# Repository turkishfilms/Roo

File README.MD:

# Roo

The Roo is a 28-key wireless split ergonomic keyboard running zmk.

This keyboard was generated using ergogen (link to ergogen)

The Original Ergogen output as well as the routed pcb files are available to tweak
as you'd like.

The default Keymap right now is an incomplete colemak dh.

## Coming Soon:
- Roo Bill Of Materials (BOM)
- QWERTY default keymap
- My full keymap 
- Hands_Down Neu
- 3d printable body files
- 3d printable case files

## Future Plans
- Hopefully a Random Number Key (ZMK devleopment incoming)
- Possibly a password enabled password manager built into the keyboard
- Parametric case and body files
- Wireless Charging
- Wireless Charging Case

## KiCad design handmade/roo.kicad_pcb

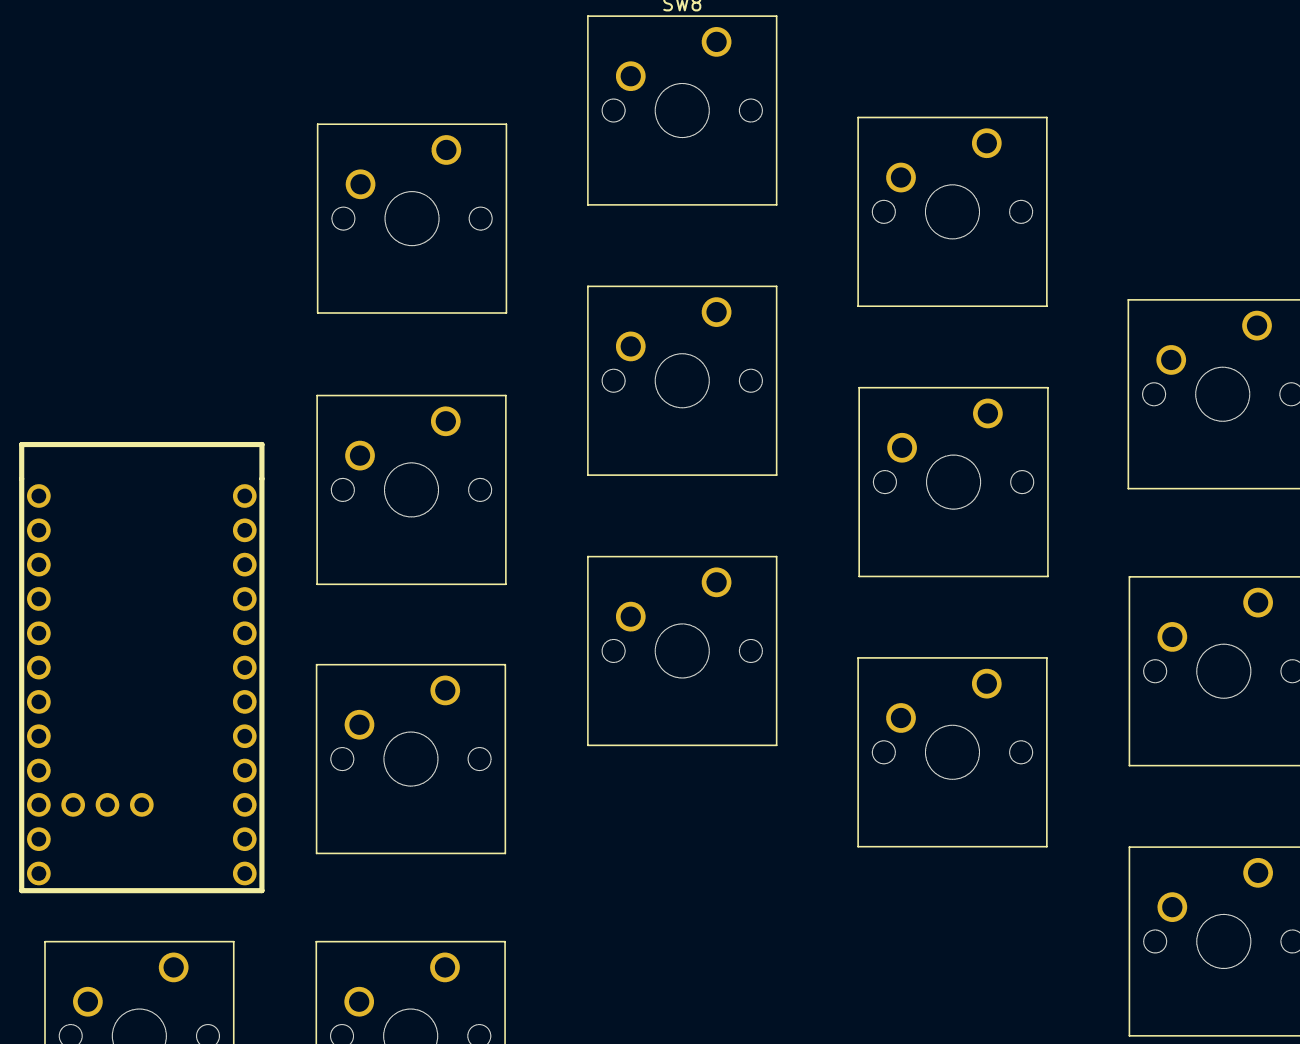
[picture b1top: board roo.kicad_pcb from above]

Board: 2 copper layers, 15 parts (0 on the bottom side), 15 nets, no tracks yet.

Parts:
SW1, SW2, SW3, SW4, SW5, SW6, SW7, SW8, SW9, SW10, SW11, SW12, SW13, SW14: SW_SPST; SW_Cherry_MX_1.00u_PCB
U1: nice_nano

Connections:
/K1: SW1.1 (A), U1.7 (P0.22)
/K2: SW2.1 (A), U1.8 (P0.24)
/K3: SW3.1 (A), U1.9 (P1.00)
/K4: SW4.1 (A), U1.10 (P0.11)
/K5: SW5.1 (A), U1.11 (P1.04)
/K6: SW6.1 (A), U1.12 (P1.06)
/K7: SW7.1 (A), U1.20 (AIN7/P0.31)
/K8: SW8.1 (A), U1.19 (AIN5/P0.29)
/K9: SW9.1 (A), U1.18 (AIN0/P0.02)
/K10: SW10.1 (A), U1.17 (P1.15)
/K11: SW11.1 (A), U1.16 (P1.13)
/K12: SW12.1 (A), U1.15 (P1.11)
/K13: SW13.1 (A), U1.14 (NFC2/P0.10)
/K14: SW14.1 (A), U1.13 (NFC1/P0.09)
GND: SW1.2 (B), SW2.2 (B), SW3.2 (B), SW4.2 (B), SW5.2 (B), SW6.2 (B), SW7.2 (B), SW8.2 (B), SW9.2 (B), SW10.2 (B), SW11.2 (B), SW12.2 (B), SW13.2 (B), SW14.2 (B)

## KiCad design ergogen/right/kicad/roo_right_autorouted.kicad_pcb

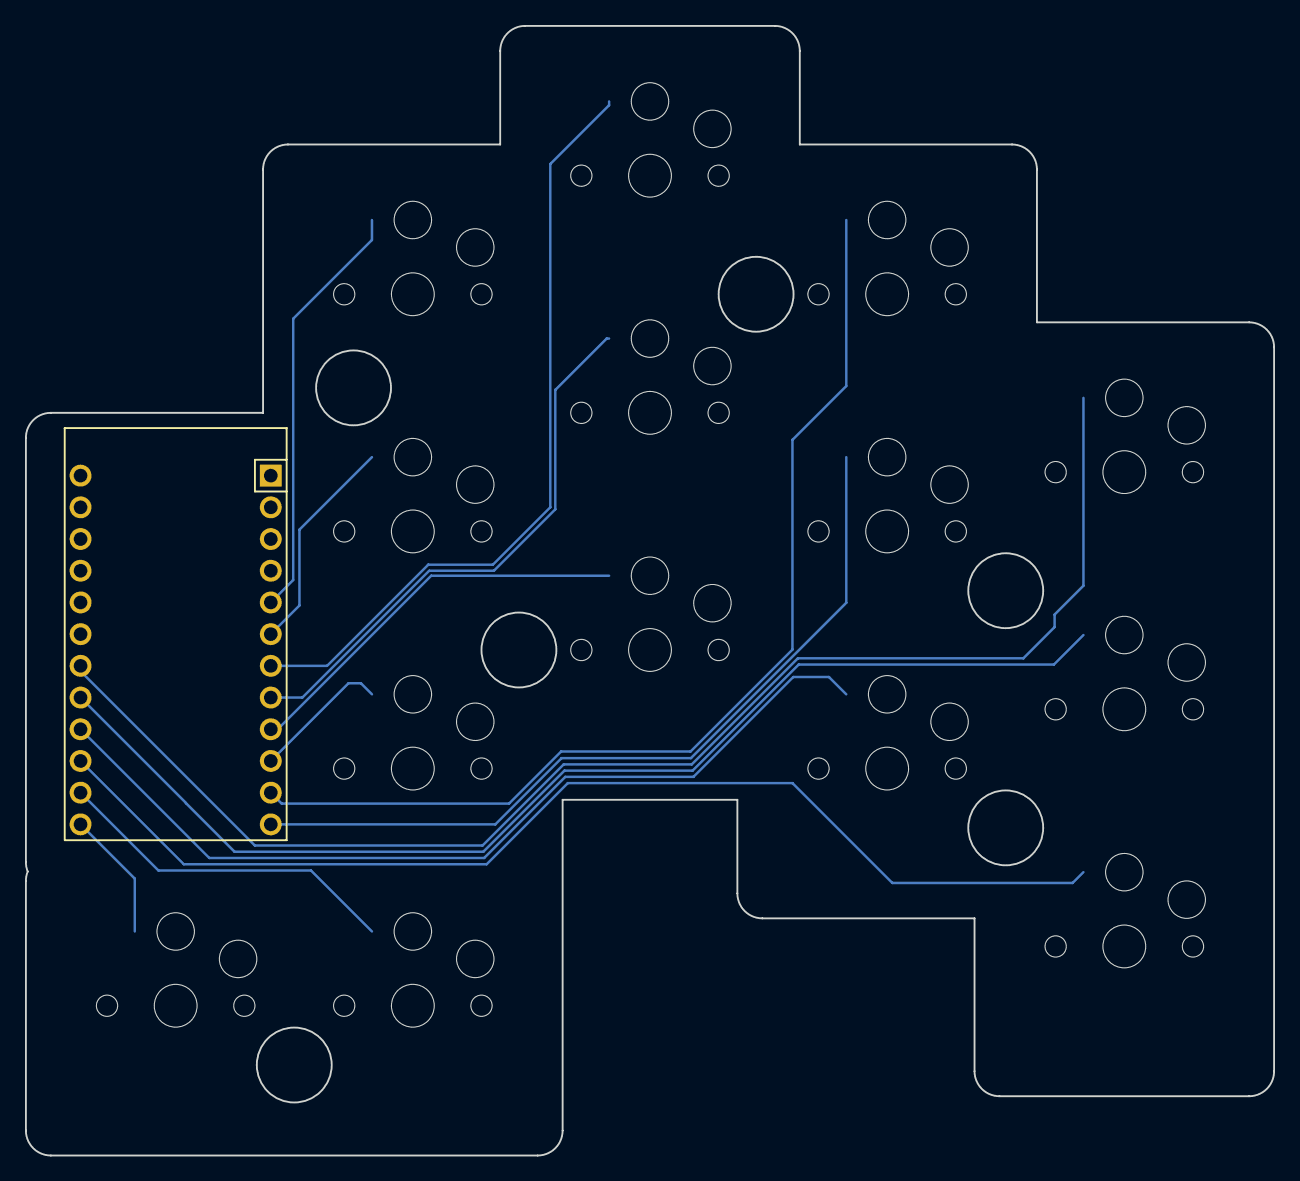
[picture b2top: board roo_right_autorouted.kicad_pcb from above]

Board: 2 copper layers, 100.0 x 90.5 mm, 15 parts (0 on the bottom side), 15 nets.

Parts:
MCU1: ProMicro
S1, S2, S3, S4, S5, S6, S7, S8, S9, S10, S11, S12, S13, S14: PG1350

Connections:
GND: MCU1.2, MCU1.15, MCU1.16, S1.2, S2.2, S3.2, S4.2, S5.2, S6.2, S7.2, S8.2, S9.2, S10.2, S11.2, S12.2, S13.2, S14.2
P4: MCU1.19, S3.1
P5: MCU1.20, S2.1
P6: MCU1.21, S4.1
P7: MCU1.22, S1.1
P8: MCU1.23, S13.1
P9: MCU1.24, S14.1
P10: MCU1.12, S5.1
P14: MCU1.10, S10.1
P15: MCU1.9, S7.1
P16: MCU1.11, S6.1
P18: MCU1.8, S8.1
P19: MCU1.7, S9.1
P20: MCU1.6, S11.1
P21: MCU1.5, S12.1

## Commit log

2024-11-15 removed shield
2024-11-15 Added shield submodule
2024-11-15 Added shield submodule URL
2024-11-15 Added README.MD
2024-11-15 updated roo_shield_module url
2024-11-15 updated roo_shield_module pointer
